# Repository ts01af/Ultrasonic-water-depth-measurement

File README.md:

# Ultrasonic-water-depth-measurement
This repository will contain KiCad project for an ultrasonic water depth measurement platform

Masterthesis.kicad_pcb is the used pcb file
Masterthesis.kicad_sch is the used schematic file

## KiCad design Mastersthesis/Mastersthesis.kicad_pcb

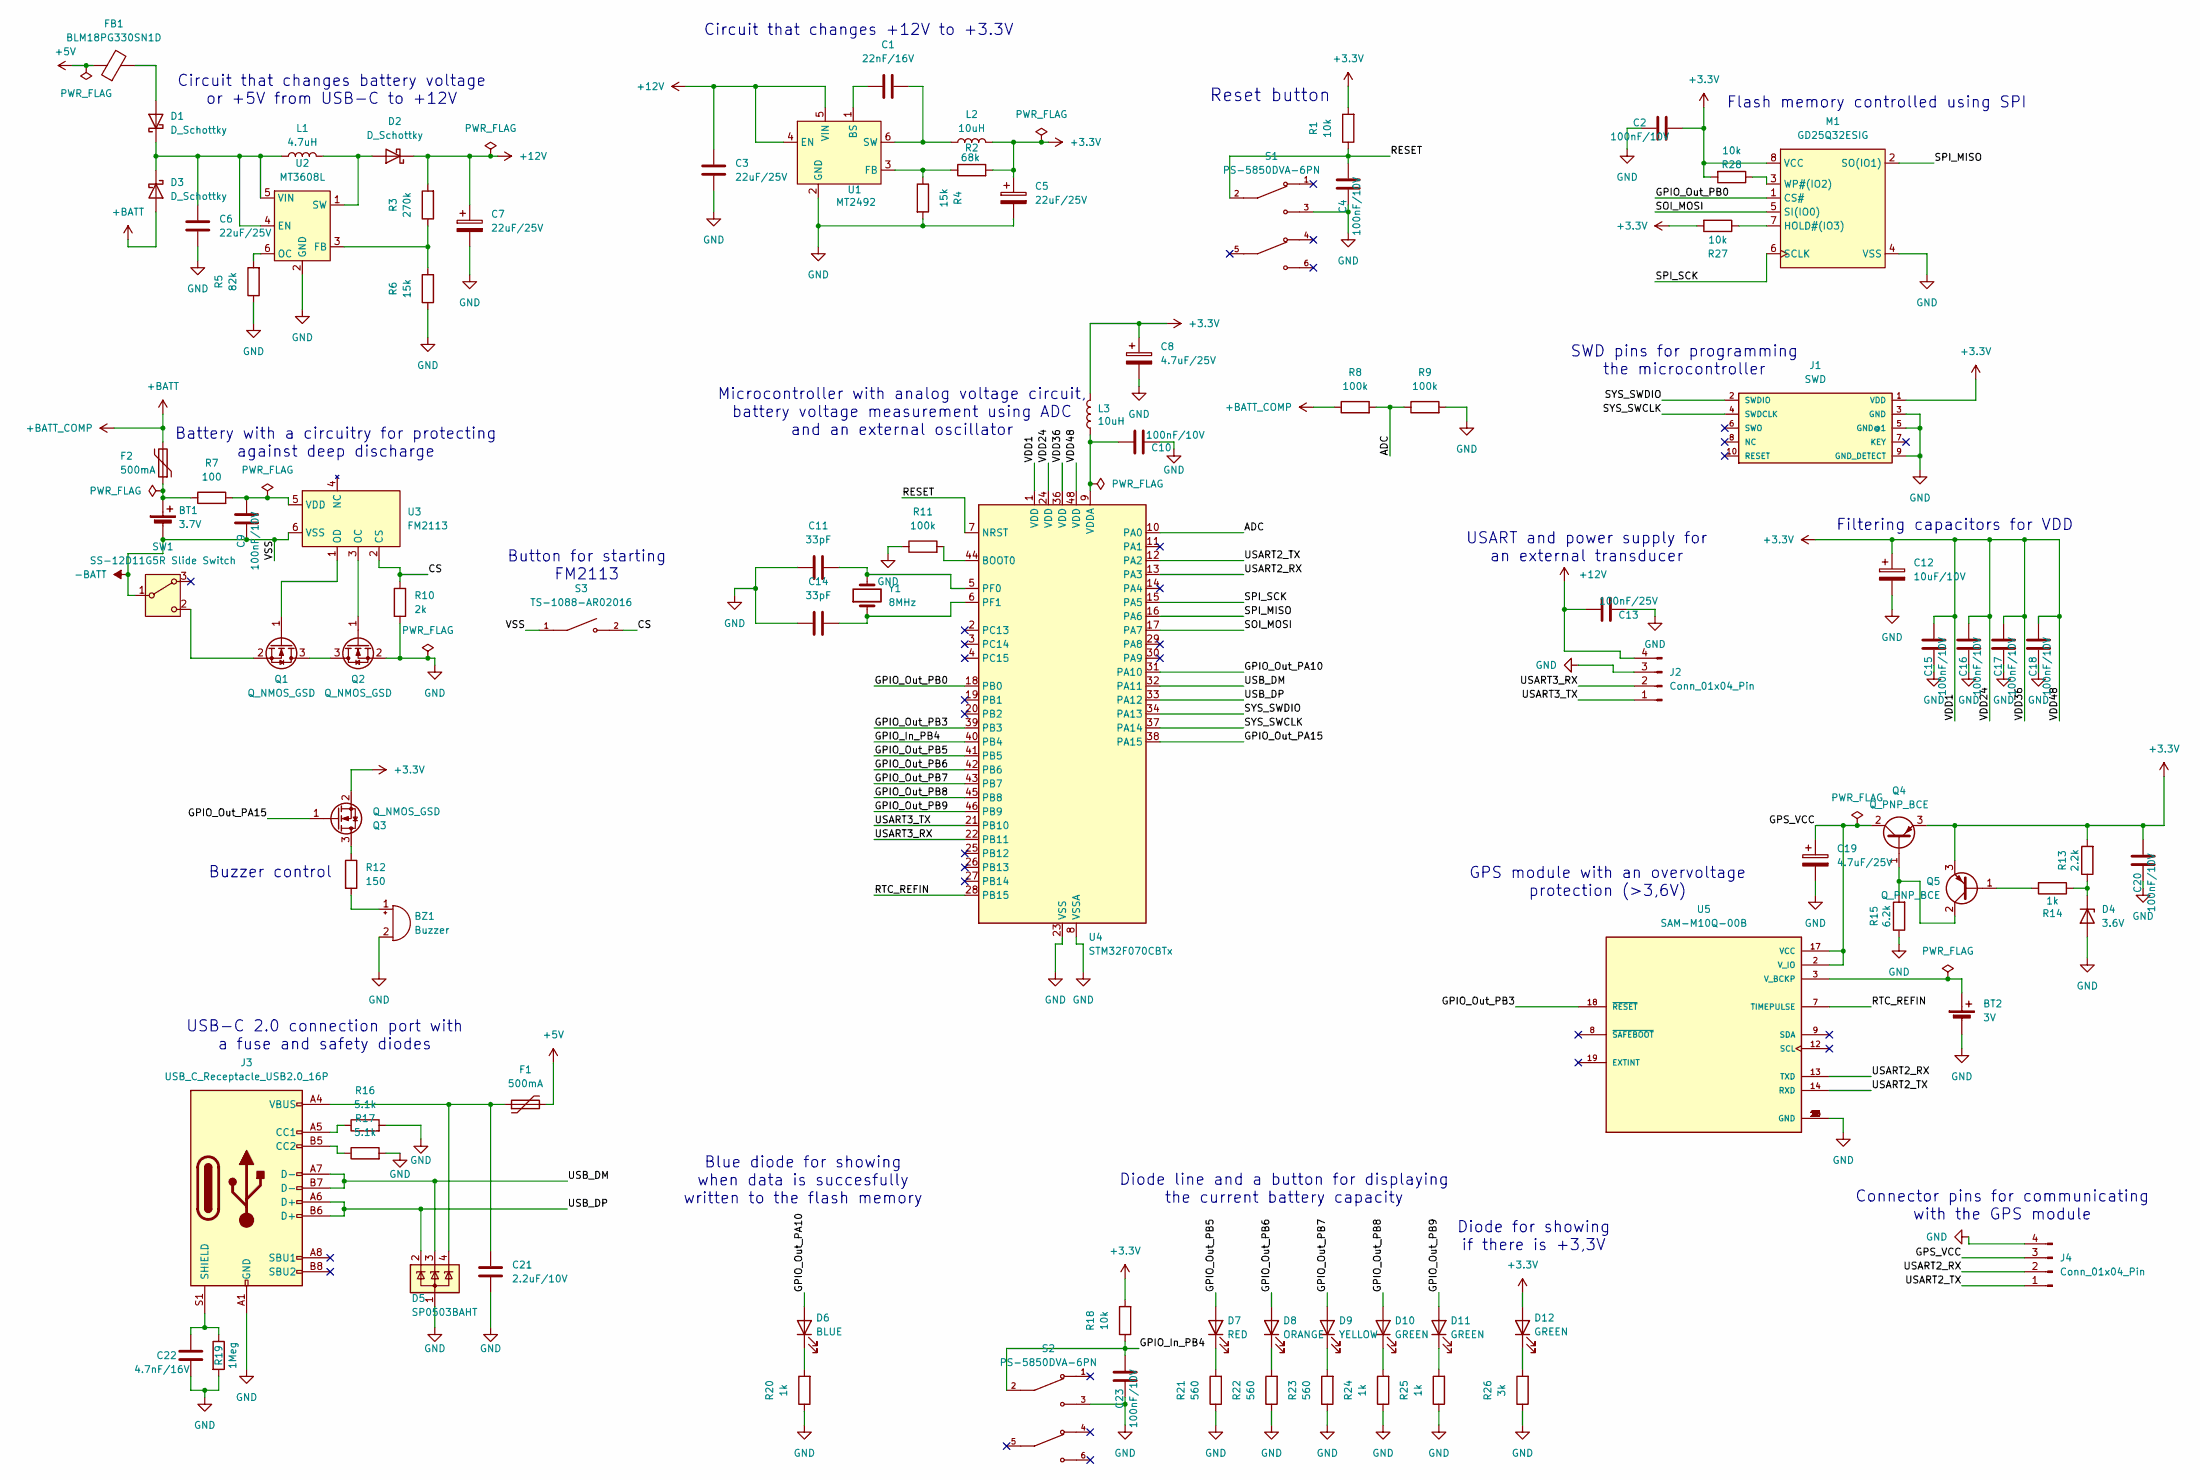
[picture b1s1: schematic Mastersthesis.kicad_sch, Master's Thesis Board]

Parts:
BT1: 3.7V; BatteryHolder_Keystone_1042_1x18650
BT2: 3V; BatteryHolder_Keystone_103_1x20mm
BZ1: Buzzer; CUI_CMI-9705-0580-SMT-TR
C1: 22nF/16V; C_0603_1608Metric
C2, C4, C9, C10, C15, C16, C17, C18, C20, C23: 100nF/10V; C_0603_1608Metric
C3, C6: 22uF/25V; C_1210_3225Metric
C5, C7: 22uF/25V; CP_Elec_5x5.4
C8, C19: 4.7uF/25V; CP_Elec_4x5.4
C11, C14: 33pF; C_0603_1608Metric
C12: 10uF/10V; CP_Elec_4x5.3
C13: 100nF/25V; C_0603_1608Metric
C21: 2.2uF/10V; C_0603_1608Metric
C22: 4.7nF/16V; C_0805_2012Metric
D1, D2, D3: D_Schottky; D_SOD-128
D4: 3.6V; D_SOD-123
D5: SP0503BAHT; SOT-143
D6: BLUE; LED_0805_2012Metric
D7: RED; LED_0805_2012Metric
D8: ORANGE; LED_0805_2012Metric
D9: YELLOW; LED_0805_2012Metric
D10, D11, D12: GREEN; LED_0805_2012Metric
F1, F2: 500mA; Fuse_0805_2012Metric
FB1: BLM18PG330SN1D; L_0603_1608Metric
J1: SWD; X1321WVS-2x05J-C40D53
J2, J4: Conn_01x04_Pin; PinHeader_1x04_P1.27mm_Vertical_SMD_Pin1Left
J3: USB_C_Receptacle_USB2.0_16P; USB_C_Receptacle_G-Switch_GT-USB-7010ASV
L1: 4.7uH; L_1008_2520Metric
L2, L3: 10uH; L_1008_2520Metric
M1: GD25Q32ESIG; SSOP-8_5.25x5.24mm_P1.27mm
Q1, Q2, Q3: Q_NMOS_GSD; SOT-23
Q4, Q5: Q_PNP_BCE; SOT-223-3_TabPin2
R1, R18, R27, R28: 10k; R_0603_1608Metric
R2: 68k; R_0603_1608Metric
R3: 270k; R_0603_1608Metric
R4, R6: 15k; R_0603_1608Metric
R5: 82k; R_0603_1608Metric
R7: 100; R_0603_1608Metric
R8, R9, R11: 100k; R_0603_1608Metric
R10: 2k; R_0603_1608Metric
R12: 150; R_0805_2012Metric
R13: 2.2k; R_0603_1608Metric
R14, R20, R24, R25: 1k; R_0805_2012Metric
R15: 6.2k; R_0603_1608Metric
R16, R17: 5.1k; R_0603_1608Metric
R19: 1Meg; R_0603_1608Metric
R21, R22, R23: 560; R_0805_2012Metric
R26: 3k; R_0805_2012Metric
S1, S2: PS-5850DVA-6PN; PARTREV E
S3: TS-1088-AR02016; SW_TS-1088-AR02016; PARTREV N/A
SW1: SS-12D11G5R Slide Switch
U1: MT2492; SOT-23-6
U2: MT3608L; SOT-23-6
U3: FM2113; SOT-23-6
U4: STM32F070CBTx; LQFP-48_7x7mm_P0.5mm
U5: SAM-M10Q-00B; XCVR_SAM-M10Q-00B; PARTREV R03
Y1: 8MHz; Crystal_SMD_HC49-SD

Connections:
+3.3V: C2.2, C5.1, C8.1, C12.1, C15.2, C16.2, C17.2, C18.2, C20.2, D12.2 (A), J1.1 (VDD), L2.2, L3.2, M1.8 (VCC), Q3.2 (S), Q4.3 (E), Q5.3 (E), R1.2, R2.2, R13.2, R18.2, R27.2, R28.2, U4.1 (VDD), U4.24 (VDD), U4.36 (VDD), U4.48 (VDD)
+5V: F1.2, FB1.1
+12V: C3.2, C7.1, C13.2, D2.1 (K), J2.4, R3.2, U1.4 (EN), U1.5 (VIN)
+BATT: D3.2 (A), F2.2, R8.1
-BATT: BT1.2 (-), C9.1, S3.1, SW1.1 (B), U3.6 (VSS)
/ADC: R8.2, R9.1, U4.10 (PA0)
/CS: R10.1, S3.2, U3.2 (CS)
/GPIO_In_PB4: C23.2, R18.1, S2.2, U4.40 (PB4)
/GPIO_Out_PA10: D6.2 (A), U4.31 (PA10)
/GPIO_Out_PA15: Q3.1 (G), U4.38 (PA15)
/GPIO_Out_PB0: M1.1 (CS#), U4.18 (PB0)
/GPIO_Out_PB3: U4.39 (PB3), U5.18 (~RESET)
/GPIO_Out_PB5: D7.2 (A), U4.41 (PB5)
/GPIO_Out_PB6: D8.2 (A), U4.42 (PB6)
/GPIO_Out_PB7: D9.2 (A), U4.43 (PB7)
/GPIO_Out_PB8: D10.2 (A), U4.45 (PB8)
/GPIO_Out_PB9: D11.2 (A), U4.46 (PB9)
/GPS_VCC: C19.1, J4.3, Q4.2 (C), U5.2 (V_IO), U5.17 (VCC)
/RESET: C4.2, R1.1, S1.2, U4.7 (NRST)
/RTC_REFIN: U4.28 (PB15), U5.7 (TIMEPULSE)
/SOI_MOSI: M1.5 (SI(IO0)), U4.17 (PA7)
/SPI_MISO: M1.2 (SO(IO1)), U4.16 (PA6)
/SPI_SCK: M1.6 (SCLK), U4.15 (PA5)
/SYS_SWCLK: J1.4 (SWDCLK), U4.37 (PA14)
/SYS_SWDIO: J1.2 (SWDIO), U4.34 (PA13)
/USART2_RX: J4.2, U4.13 (PA3), U5.13 (TXD)
/USART2_TX: J4.1, U4.12 (PA2), U5.14 (RXD)
/USART3_RX: J2.2, U4.22 (PB11)
/USART3_TX: J2.1, U4.21 (PB10)
/USB_DM: D5.3 (K), J3.A7 (D-), J3.B7 (D-), U4.32 (PA11)
/USB_DP: D5.2 (K), J3.A6 (D+), J3.B6 (D+), U4.33 (PA12)
GND: BT2.2 (-), BZ1.2 (-), C2.1, C3.1, C4.1, C5.2, C6.1, C7.2, C8.2, C10.1, C11.1, C12.2, C13.1, C14.1, C15.1, C16.1, C17.1, C18.1, C19.2, C20.1, C21.1, C22.2, C23.1, D4.2 (A), D5.1 (A), J1.3 (GND), J1.5 (GND@1), J1.9 (GND_DETECT), J2.3, J3.A1 (GND), J3.A12 (GND), J3.B1 (GND), J3.B12 (GND), J4.4, M1.4 (VSS), Q2.2 (S), R4.2, R5.1, R6.1, R9.2, R10.2, R11.1, R15.1, R16.2, R17.2, R19.2, R20.1, R21.1, R22.1, R23.1, R24.1, R25.1, R26.1, S1.3, S2.3, U1.2 (GND), U2.2 (GND), U4.8 (VSSA), U4.23 (VSS), U4.35 (VSS), U4.47 (VSS), U5.1 (GND), U5.4 (GND), U5.5 (GND), U5.6 (GND), U5.10 (GND), U5.11 (GND), U5.15 (GND), U5.16 (GND), U5.20 (GND)
unnamed: BT1.1 (+), F2.1, R7.1
unnamed: BT2.1 (+), U5.3 (V_BCKP)
unnamed: BZ1.1 (+), R12.2
unnamed: C21.2, D5.4 (K), F1.1, J3.A4 (VBUS), J3.A9 (VBUS), J3.B4 (VBUS), J3.B9 (VBUS)
unnamed: D1.2 (A), FB1.2
unnamed: C6.2, D1.1 (K), D3.1 (K), L1.1, U2.4 (EN), U2.5 (VIN)
unnamed: D2.2 (A), L1.2, U2.1 (SW)
unnamed: D4.1 (K), R13.1, R14.1
unnamed: D6.1 (K), R20.2
unnamed: D7.1 (K), R21.2
unnamed: D8.1 (K), R22.2
unnamed: D9.1 (K), R23.2
unnamed: D10.1 (K), R24.2
unnamed: D11.1 (K), R25.2
unnamed: D12.1 (K), R26.2
unnamed: J3.A5 (CC1), R16.1
unnamed: J3.B5 (CC2), R17.1
unnamed: C22.1, J3.S1 (SHIELD), R19.1
unnamed: M1.7 (HOLD#(IO3)), R27.1
unnamed: M1.3 (WP#(IO2)), R28.1
unnamed: Q1.3 (D), Q2.3 (D)
unnamed: Q1.1 (G), U3.1 (OD)
unnamed: Q1.2 (S), SW1.2 (C)
unnamed: Q2.1 (G), U3.3 (OC)
unnamed: Q3.3 (D), R12.1
unnamed: Q4.1 (B), Q5.2 (C), R15.2
unnamed: Q5.1 (B), R14.2
unnamed: C1.2, U1.1 (BS)
unnamed: R2.1, R4.1, U1.3 (FB)
unnamed: C1.1, L2.1, U1.6 (SW)
unnamed: R3.1, R6.2, U2.3 (FB)
unnamed: R5.2, U2.6 (OC)
unnamed: C9.2, R7.2, U3.5 (VDD)
unnamed: R11.2, U4.44 (BOOT0)
unnamed: C11.2, U4.5 (PF0), Y1.2
unnamed: C14.2, U4.6 (PF1), Y1.1
unnamed: C10.2, L3.1, U4.9 (VDDA)

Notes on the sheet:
Connector pins for communicating with the GPS module
SWD pins for programming the microcontroller
Circuit that changes +12V to +3.3V
Microcontroller with analog voltage circuit, battery voltage measurement using ADC and an external oscillator
Circuit that changes battery voltage or +5V from USB-C to +12V
GPS module with an overvoltage protection (>3,6V)
Button for starting FM2113
Buzzer control
Flash memory controlled using SPI
Diode line and a button for displaying the current battery capacity
Filtering capacitors for VDD
Blue diode for showing when data is succesfully written to the flash memory
USART and power supply for an external transducer
Diode for showing if there is +3,3V
Reset button
Battery with a circuitry for protecting against deep discharge
USB-C 2.0 connection port with a fuse and safety diodes

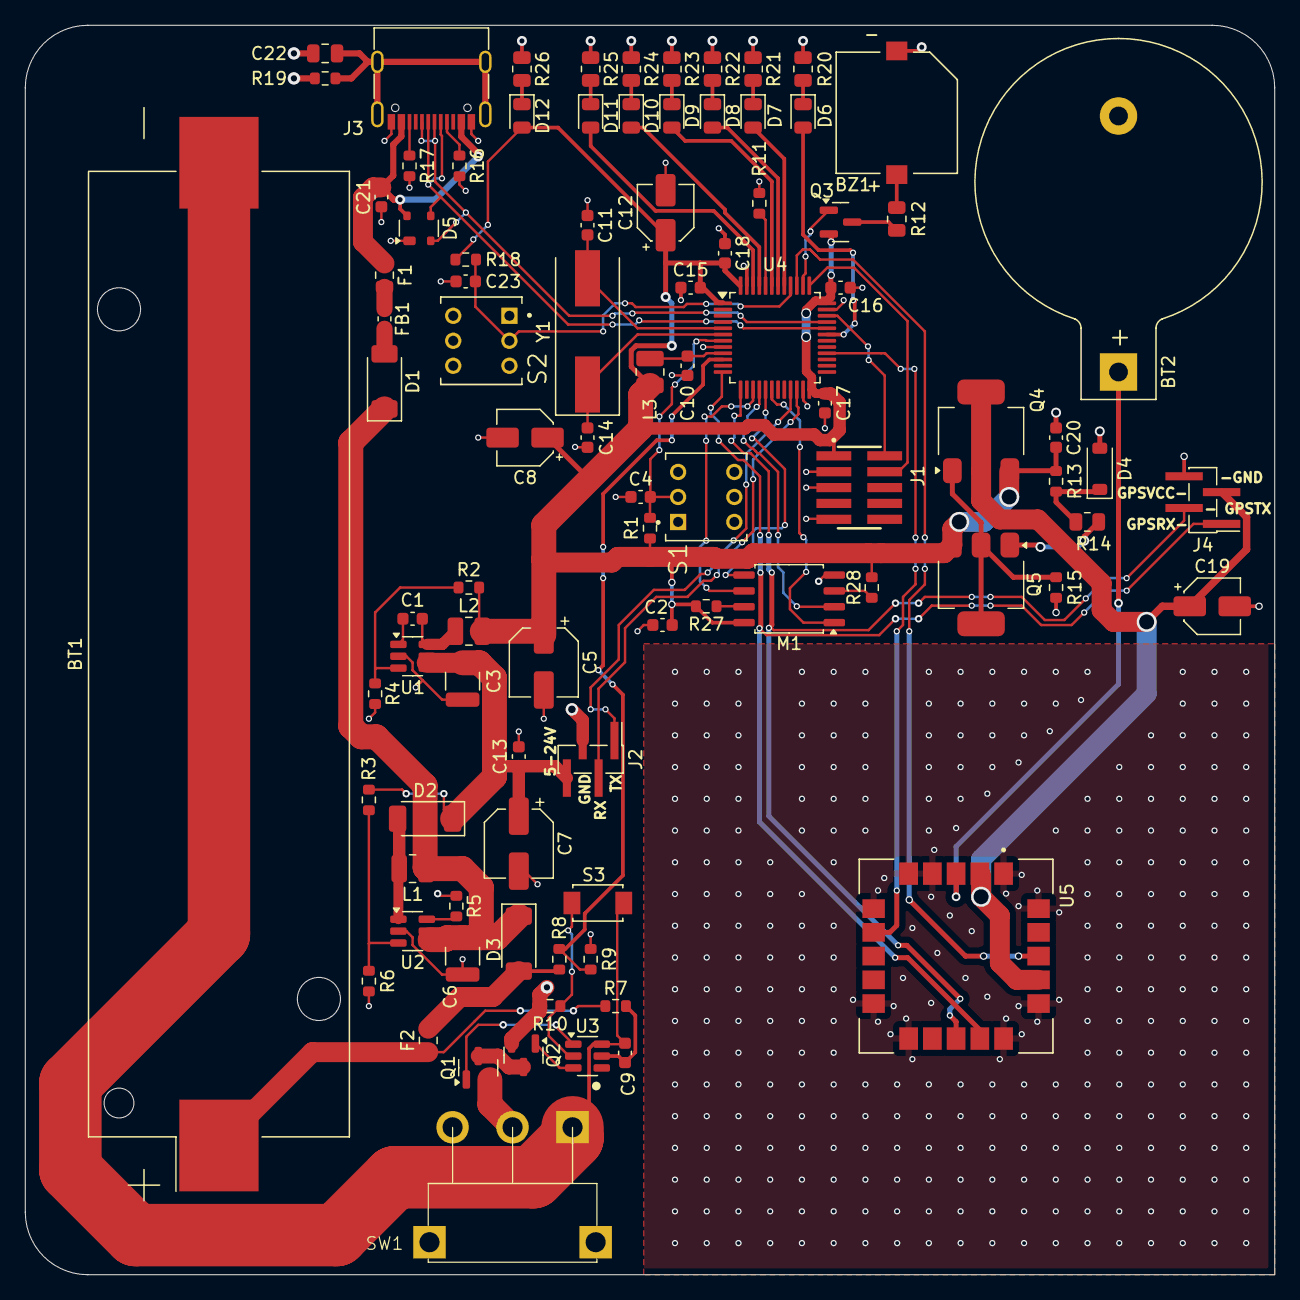
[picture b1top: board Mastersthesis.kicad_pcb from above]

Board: 2 copper layers, 100.0 x 100.0 mm, 92 parts (0 on the bottom side), 69 nets.

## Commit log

2025-07-24 Added full project with own library files
    Full project consisting of pcb, schematics, local library elements and layers.
